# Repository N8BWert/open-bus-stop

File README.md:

# Informal Bus Display

## Motivation

While traveling abroad, I noticed that a lot of cities (specifically in the Netherlands) have displays at bus stops detailing the next bus arrival.  This is relatively unheard of in the United States (except for at certain Bus Rapid Transit stations) so I figured it would be interesting to create an informal bus display.  This informal bus display is a simple LCD screen attached to a low-powered microcontroller, but we can use the RTC to try to display the next bus arrivals.

## Description

To make the bus riding experience more enjoyable and reliable, a small low-powered microcontroller display can be created to display the static arrival times of buses.  These displays can be created inexpensively and placed throughout the city informally by residents to aid bus riders in knowing when their next bus is scheduled.

To further extend this concept, our team is also looking to create a set of "towers" (raspberry pis) that can relay real-time bus arrival schedules to the low-powered displays via LoRA radios as well as creating a mapping software to display the location of the various bus-stop displays and "towers" to visualize the adoption of the informal bus stop displays.

## Technical Details

A small low-power microcontroller can be attached at each bus stop around the city.  The microcontroller will have the static table of the bus arrival times for the given bus stop.  Additionally, to improve the accuracy of the microcontroller displays a second “tower” can be created from a raspberry pi and a LoRA-capable radio.  The raspberry pi can ping the relevant transit agency’s API to determine the real-time bus arrival times for all bus stations in its local range.  Then it can relay this information via a LoRA radio to the low-power microcontroller displays to give them real-time bus arrival data.  To contribute to the formation of an informal network of the bus displays and towers a web app can be created.  The towers will relay their GPS coordinate as well as the bus stops they are serving to the web application which can create an autonomic map of the serviced area of the informal bus displays.  Additionally, the low-power microcontrollers will still be able to display static bus arrival times when not connected via LoRA, but will need to be manually registered with the central website to be displayed.

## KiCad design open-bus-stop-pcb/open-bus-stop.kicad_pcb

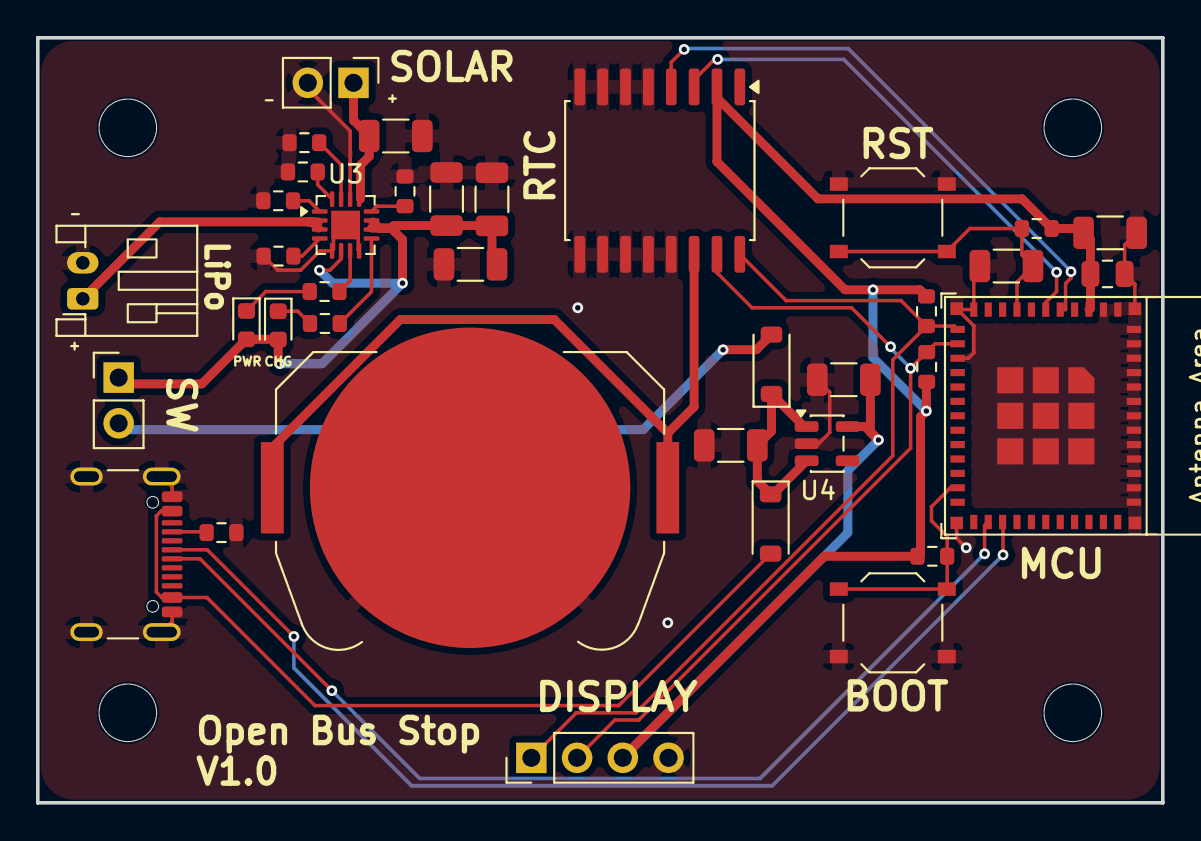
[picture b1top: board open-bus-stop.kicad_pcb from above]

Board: 2 copper layers, 62.5 x 42.5 mm, 41 parts (0 on the bottom side), 27 nets.

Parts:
BT1: CR1220; BatteryHolder_Keystone_3034_1x20mm
C1, C2, C3, C4, C9: 10uF; C_1206_3216Metric
C5, C6, C7: 1uF; C_1206_3216Metric
C8: 0.1uF; C_0805_2012Metric
D1: GREEN; LED_0603_1608Metric
D2: RED; LED_0603_1608Metric
D3, D4: D_Schottky; D_SOD-123
H1, H2, H3, H4: MountingHole; MountingHole_3.2mm_M3
J1: Conn_01x04_Pin; PinHeader_1x04_P2.54mm_Vertical
J2: Conn_01x02_Pin; PinHeader_1x02_P2.54mm_Vertical
J3: Conn_01x02; JST_PH_S2B-PH-K_1x02_P2.00mm_Horizontal
J5: Conn_01x02; PinHeader_1x02_P2.54mm_Vertical
P1: USB_C_Plug_USB2.0; USB_C_Receptacle_GCT_USB4105-xx-A_16P_TopMnt_Horizontal
R1, R2, R9: 4.7k; R_0603_1608Metric
R3, R4, R5, R6, R11, R12: 10k; R_0603_1608Metric
R7: 1k; R_0603_1608Metric
R8: 6.2k; R_0603_1608Metric
R10: 5.1k; R_0603_1608Metric
SW2, SW4: SW_Push; SW_Push_1P1T_XKB_TS-1187A
U1: ESP32-C3-MINI-1
U2: DS3231M; SOIC-16W_7.5x10.3mm_P1.27mm
U3: BQ24074RGT; VQFN-16-1EP_3x3mm_P0.5mm_EP1.6x1.6mm
U4: ME6211C33M5; SOT-23-5

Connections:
/D+: P1.A6 (D+), U1.27 (GPIO19/USB_D+)
/D-: P1.A7 (D-), U1.26 (GPIO18/USB_D-)
/RTC_nIRQ: U1.6 (GPIO3/ADC1_CH3), U2.3 (~INT/SQW)
/RTC_nRST: U1.5 (GPIO2/ADC1_CH2), U2.4 (~RST)
/SCL: J1.2, R2.1, U1.13 (GPIO1/ADC1_CH1/XTAL_32K_N), U2.15 (SDA)
/SDA: J1.1, R1.1, U1.12 (GPIO0/ADC1_CH0/XTAL_32K_P), U2.16 (SCL)
/V_BAT: J3.1, U3.2 (BAT), U3.3 (BAT)
/V_IN: C1.2, C2.2, C3.2, D1.2 (A), D2.2 (A), J5.1, U3.6 (EN1), U3.10 (OUT), U3.11 (OUT)
/V_SOL: C4.1, J2.1, U3.13 (IN)
/V_USB: D4.2 (A), P1.A4 (VBUS), P1.A9 (VBUS), P1.B4 (VBUS), P1.B9 (VBUS)
GND: BT1.2 (-), C1.1, C2.1, C3.1, C4.2, C5.2, C6.2, C7.1, C8.1, C9.1, J1.4, J2.2, J3.2, P1.A1 (GND), P1.A12 (GND), P1.B1 (GND), P1.B12 (GND), P1.SH (SHIELD), R5.2, R6.2, R7.2, R8.2, R9.1, R10.1, SW2.1, SW4.2, U1.1 (GND), U1.2 (GND), U1.11 (GND), U1.14 (GND), U1.36 (GND), U1.37 (GND), U1.38 (GND), U1.39 (GND), U1.40 (GND), U1.41 (GND), U1.42 (GND), U1.43 (GND), U1.44 (GND), U1.45 (GND), U1.46 (GND), U1.47 (GND), U1.48 (GND), U1.49 (GND), U1.50 (GND), U1.51 (GND), U1.52 (GND), U1.53 (GND), U2.5 (GND), U2.6 (GND), U2.7 (GND), U2.8 (GND), U2.9 (GND), U2.10 (GND), U2.11 (GND), U2.12 (GND), U2.13 (GND), U3.5 (EN2), U3.8 (VSS), U3.14 (TMR), U3.17 (VSS), U4.2 (V_{SS})
unnamed: BT1.1 (+), U2.14 (VBAT)
unnamed: D1.1 (K), R3.1
unnamed: D2.1 (K), R4.2
unnamed: D3.2 (A), J5.2
unnamed: C5.1, D3.1 (K), D4.1 (K), U4.1 (V_{IN}), U4.3 (CE)
unnamed: P1.A5 (CC), R10.2
unnamed: C7.2, R12.2, SW2.2, U1.8 (EN/CHIP_PU)
unnamed: R11.1, SW4.1, U1.23 (GPIO9)
unnamed: R7.1, U3.12 (ILIM)
unnamed: R8.1, U3.16 (ISET)
unnamed: R9.2, U3.15 (ITERM)
unnamed: R5.1, U3.1 (TS)
unnamed: R6.1, U3.4 (~CE)
unnamed: R4.1, U3.9 (~CHG)
unnamed: R3.2, U3.7 (~PGOOD)
VCC: C6.1, C8.2, C9.2, J1.3, R1.2, R2.2, R11.2, R12.1, U1.3 (3V3), U2.2 (VCC), U4.5 (V_{OUT})

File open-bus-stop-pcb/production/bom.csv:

Designator,Footprint,Quantity,Value,LCSC Part #
BT1,BatteryHolder_Keystone_3034_1x20mm,1,CR1220,
"C1, C2, C3, C4, C9",1206,5,10uF,
"C5, C6, C7",1206,3,1uF,
C8,0805,1,0.1uF,
D1,0603,1,GREEN,
D2,0603,1,RED,
"D3, D4",D_SOD-123,2,D_Schottky,
J1,PinHeader_1x04_P2.54mm_Vertical,1,Conn_01x04_Pin,
J2,PinHeader_1x02_P2.54mm_Vertical,1,Conn_01x02_Pin,
J3,JST_PH_S2B-PH-K_1x02_P2.00mm_Horizontal,1,Conn_01x02,
J5,PinHeader_1x02_P2.54mm_Vertical,1,Conn_01x02,
P1,USB_C_Receptacle_GCT_USB4105-xx-A_16P_TopMnt_Horizontal,1,USB_C_Plug_USB2.0,
"R1, R2, R9",0603,3,4.7k,
R10,0603,1,5.1k,
"R11, R12, R3, R4, R5, R6",0603,6,10k,
R7,0603,1,1k,
R8,0603,1,6.2k,
"SW2, SW4",SW_Push_1P1T_XKB_TS-1187A,2,SW_Push,
U1,ESP32-C3-MINI-1,1,ESP32-C3-MINI-1,
U2,SOIC-16W_7.5x10.3mm_P1.27mm,1,DS3231M,
U3,VQFN-16-1EP_3x3mm_P0.5mm_EP1.6x1.6mm,1,BQ24074RGT,
U4,SOT-23-5,1,ME6211C33M5,

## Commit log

2026-06-12 Initialize Repo after Receiving Approval
2026-06-12 test display library with rp2040. Things are working on the display end. Time to get some data
2026-06-13 build basic bus display enclosure in FreeCAD
2026-06-13 write GTFS static transit data parser
2026-06-13 working static transit arrival display
2026-06-13 remove test prints, flash over usb, display time
2026-06-14 Start working on production version
2026-06-14 (WIP) swapping RTCs and Display to decrease BOM cost
